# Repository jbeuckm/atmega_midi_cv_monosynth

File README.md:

arduino_midi_cv
===============

Uses the Arduino MIDI library to operate two x MCP4822 12-bit DAC with internal voltage reference.

Largely based on http://www.experimentalistsanonymous.com/ve3wwg/doku.php?id=analog_synth_midi

Uses 4922 library from http://www.alhin.de/arduino

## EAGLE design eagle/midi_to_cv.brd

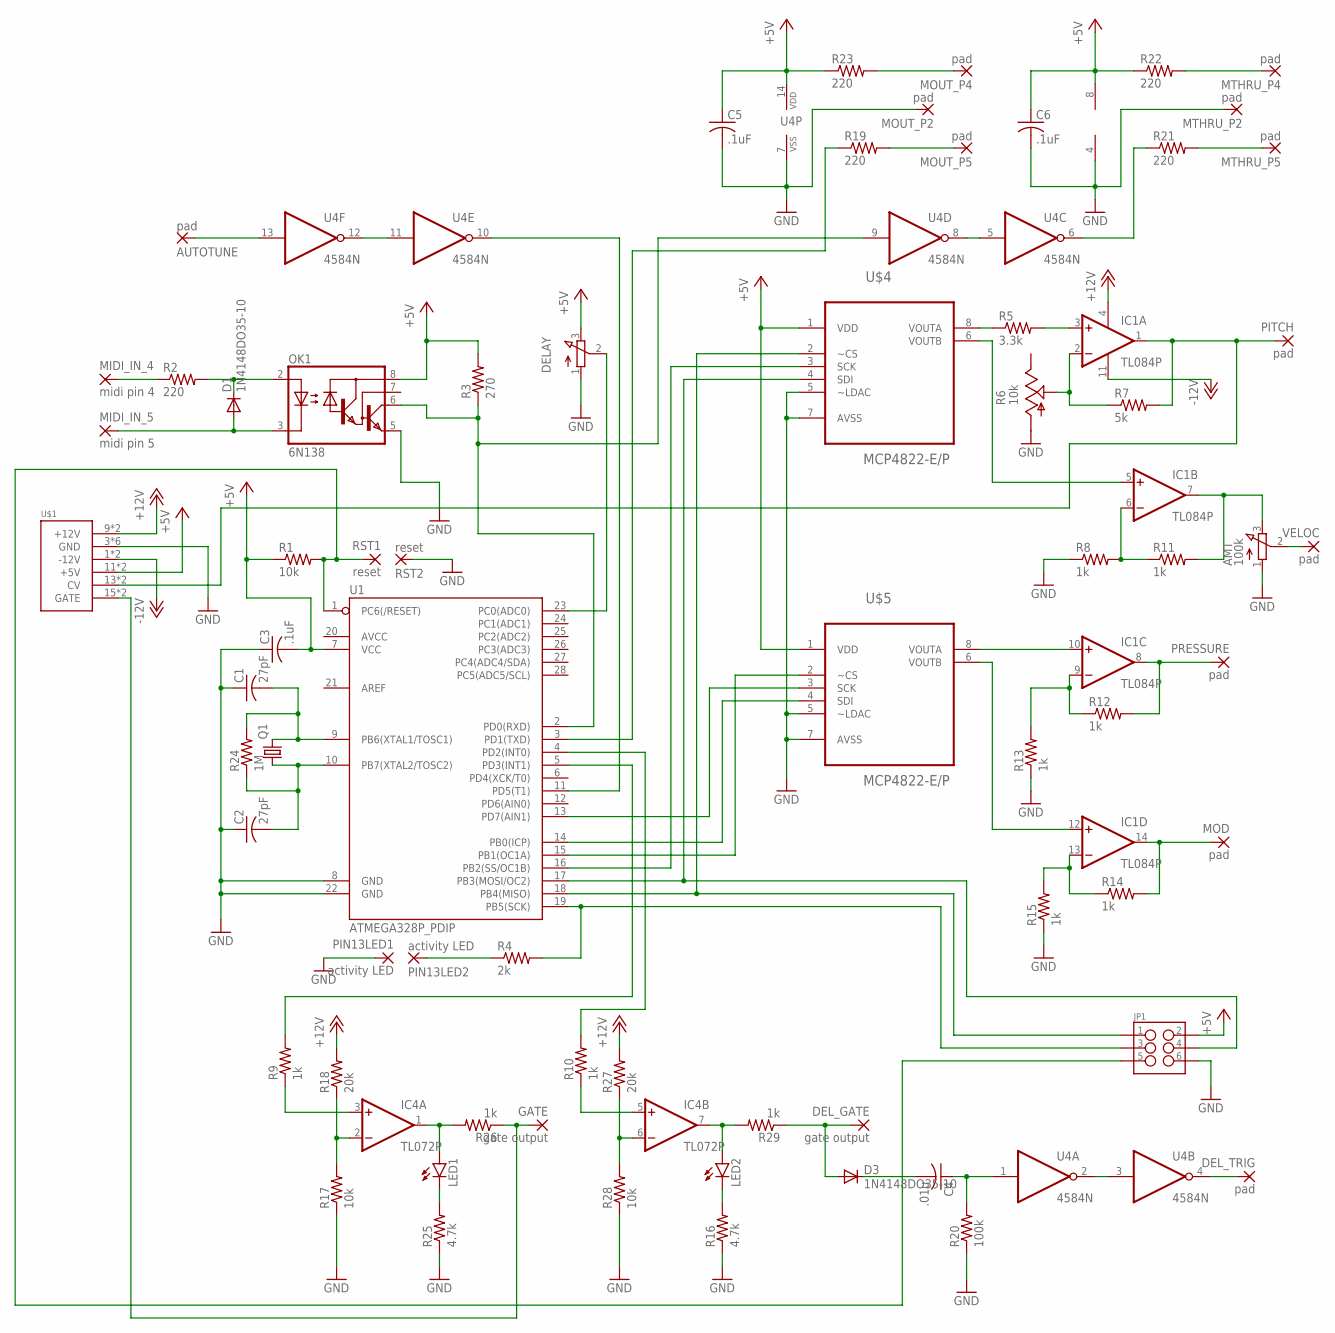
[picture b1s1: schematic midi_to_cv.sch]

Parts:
AMT: 100k; 3RP/1610N
AUTOTUNE: pad; 2,54/0,9
C1, C2: 27pF; C025-040X050
C3, C5, C6: .1uF; C050-024X044
C4: .01u; C050-024X044
D1, D3: 1N4148DO35-10; DO35-10
DELAY: 3RP/1610N
DEL_GATE: gate output; 2,54/0,9
DEL_TRIG: pad; 2,54/0,9
GATE: gate output; 2,54/0,9
IC1: TL084P; DIL14
IC4: TL072P; DIL08
JP1: M03X2NO_SILK; 2X3-NS
LED1, LED2: LED3MM
MIDI_IN_4: midi pin 4; 2,54/0,9
MIDI_IN_5: midi pin 5; 2,54/0,9
MOD: pad; 2,54/0,9
MOUT_P2, MOUT_P4, MOUT_P5: pad; 2,54/0,9
MTHRU_P2, MTHRU_P4, MTHRU_P5: pad; 2,54/0,9
OK1: 6N138; DIL08
PIN13LED1, PIN13LED2: activity LED; 2,54/0,9
PITCH: pad; 2,54/0,9
PRESSURE: pad; 2,54/0,9
Q1: CRYSTALHC33U-V; HC33U-V
R1, R17, R28: 10k; 0207/10
R2, R19, R21, R22, R23: 220; 0207/10
R3: 270; 0207/10
R4: 2k; 0207/10
R5: 3.3k; 0207/10
R6: 10k; B64W
R7: 5k; 0207/10
R8, R9, R10, R11, R12, R13, R14, R15, R26, R29: 1k; 0207/10
R16, R25: 4.7k; 0207/10
R18, R27: 20k; 0207/10
R20: 100k; 0207/10
R24: 1M; 0207/10
RST1, RST2: reset; 2,54/0,9
U1: ATMEGA328P_PDIP; DIL28-3
U4: 4584N; DIL14
U$1: POWER; POWER_16
U$4, U$5: MCP4822-E/P; DIP254P762X432-8
VELOC: pad; 2,54/0,9

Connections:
+5V: C3.2, C5.1, C6.1, DELAY.3 (E), IC4.8 (V+), JP1.2, OK1.8 (VCC), R1.1, R3.2, R22.1, R23.1, U1.7 (VCC), U4.14 (VDD), U$1.11 (+5V), U$1.12 (+5V), U$4.1 (VDD), U$5.1 (VDD)
+12V: IC1.4 (V+), R18.2, R27.2, U$1.9 (+12V), U$1.10 (+12V)
-12V: IC1.11 (V-), U$1.1 (-12V), U$1.2 (-12V)
GND: AMT.1 (A), C1.1, C2.1, C3.1, C5.2, C6.2, DELAY.1 (A), IC4.4 (V-), JP1.6, MOUT_P2.1, MTHRU_P2.1, OK1.5 (GND), PIN13LED1.1, R6.A, R8.1, R13.1, R15.1, R16.1, R17.1, R20.1, R25.1, R28.1, RST2.1, U1.8 (GND), U1.22 (GND), U4.7 (VSS), U$1.3 (GND), U$1.4 (GND), U$1.5 (GND), U$1.6 (GND), U$1.7 (GND), U$1.8 (GND), U$4.5 (~LDAC), U$4.7 (AVSS), U$5.5 (~LDAC), U$5.7 (AVSS)
unnamed: IC4.3 (+IN), R9.1
unnamed: R5.1, U$4.8 (VOUTA)
unnamed: D1.A, MIDI_IN_5.1, OK1.3 (C)
unnamed: C1.2, Q1.2, R24.2, U1.9 (PB6(XTAL1/TOSC1))
unnamed: C2.2, Q1.1, R24.1, U1.10 (PB7(XTAL2/TOSC2))
unnamed: IC1.3 (+IN), R5.2
unnamed: D1.C, OK1.2 (A), R2.2
unnamed: MIDI_IN_4.1, R2.1
unnamed: IC1.1 (OUT), PITCH.1, R7.2, U$1.13 (CV), U$1.14 (CV)
unnamed: JP1.3, R4.2, U1.19 (PB5(SCK))
unnamed: PIN13LED2.1, R4.1
unnamed: IC1.2 (-IN), R6.S, R7.1
unnamed: IC1.6 (-IN), R8.2, R11.1
unnamed: IC1.5 (+IN), U$4.6 (VOUTB)
unnamed: IC4.2 (-IN), R17.2, R18.1
unnamed: IC4.1 (OUT), LED1.A, R26.2
unnamed: AMT.3 (E), IC1.7 (OUT), R11.2
unnamed: IC1.10 (+IN), U$5.8 (VOUTA)
unnamed: IC1.8 (OUT), PRESSURE.1, R12.2
unnamed: IC1.9 (-IN), R12.1, R13.2
unnamed: IC1.14 (OUT), MOD.1, R14.2
unnamed: IC1.13 (-IN), R14.1, R15.2
unnamed: U1.14 (PB0(ICP)), U$5.4 (SDI)
unnamed: IC1.12 (+IN), U$5.6 (VOUTB)
unnamed: U1.16 (PB2(SS/OC1B)), U$4.3 (SCK)
unnamed: JP1.4, U1.17 (PB3(MOSI/OC2)), U$4.4 (SDI)
unnamed: DELAY.2 (S), U1.23 (PC0(ADC0))
unnamed: U1.13 (PD7(AIN1)), U$5.3 (SCK)
unnamed: U1.15 (PB1(OC1A)), U$5.2 (~CS)
unnamed: OK1.6 (VO), R3.1, U1.2 (PD0(RXD)), U4.9 (I)
unnamed: GATE.1, R26.1, U$1.15 (GATE), U$1.16 (GATE)
unnamed: R10.2, U1.4 (PD2(INT0))
unnamed: R9.2, U1.5 (PD3(INT1))
unnamed: AUTOTUNE.1, U4.13 (I)
unnamed: D3.A, DEL_GATE.1, R29.1
unnamed: LED2.K (C), R16.2
unnamed: U4.11 (I), U4.12 (O)
unnamed: U1.11 (PD5(T1)), U4.10 (O)
unnamed: U4.5 (I), U4.8 (O)
unnamed: U4.2 (O), U4.3 (I)
unnamed: C4.1, R20.2, U4.1 (I)
unnamed: IC4.5 (+IN), R10.1
unnamed: JP1.5, R1.2, RST1.1, U1.1 (PC6(/RESET))
unnamed: IC4.6 (-IN), R27.1, R28.2
unnamed: JP1.1, U1.18 (PB4(MISO)), U$4.2 (~CS)
unnamed: MOUT_P5.1, R19.2
unnamed: LED1.K (C), R25.2
unnamed: C4.2, D3.C
unnamed: DEL_TRIG.1, U4.4 (O)
unnamed: R21.1, U4.6 (O)
unnamed: AMT.2 (S), VELOC.1
unnamed: MTHRU_P5.1, R21.2
unnamed: IC4.7 (OUT), LED2.A, R29.2
unnamed: MTHRU_P4.1, R22.2
unnamed: MOUT_P4.1, R23.2
unnamed: R19.1, U1.3 (PD1(TXD))

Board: 2 copper layers, 71 parts (0 on the bottom side), 60 nets, no tracks yet.

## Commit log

2014-10-13 delay gate off if another key still pressed
2014-10-25 restructured by arduino
2014-11-09 set pitch and velocity cv before trigger
2014-11-16 adding cambam and eagle files
2014-11-17 adding four programmable gates outputs
2014-11-18 trying to autoroute
2014-11-21 power to the op amps
2014-11-21 toward a routing for the gates
2014-11-23 changed readme to reflect internally referenced 4822
2014-12-06 routed with jumpers for gates and one via
2014-12-15 conforming to the schematic
2014-12-15 gates 3 and 4 operating
2014-12-16 corrected to smaller xtal package
2014-12-16 photo
2014-12-17 will add iscp header
2015-06-18 this interface is getting sirius
2015-09-03 updated gate circuits and normalled gate and cv to power connector and swapped vel and mod outputs
2015-09-03 gitignore
2015-09-03 parts basically on board and 072 powered
2015-09-04 swapped some gates and rearranged to layout
2015-09-04 arranged power to the right and getting close to routed
2015-09-05 ready to cut layout
2015-09-06 prototype coming alive with this software update
2015-09-06 started a panel
2015-09-07 basic delay code working
2015-09-07 good delay handling
2015-09-07 cam of panel

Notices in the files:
parts and their libraries:
SparkFun-DigitalIC: Licensing: Creative Commons ShareAlike 4.0 International - https://creativecommons.org/licenses/by-sa/4.0
